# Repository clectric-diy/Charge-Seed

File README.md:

This breakout board is available for purchase at [store.clectric.diy](https://store.clectric.diy).

## Design
Our goal is to create a breakout board that includes the pinout diagram so that you have the reference information that you need to work with the Daisy Seed.

### 2D Render

### 3D Render

### Caveat
The PCB fabricator that we use requires the use of their proprietary software to add the images, so while the images are available here, there are extra steps to put them on the board.

## Feedback
Constructive [feedback](https://github.com/orgs/clectric-diy/discussions/categories/charge-seed-q-a) is welcome!

## License
This project is open hardware under the [CERN-OHL-S](https://gitlab.com/ohwr/project/cernohl/-/wikis/uploads/b236492596cfc91c12def7d50bbf7da0/cern_ohl_s_v2.pdf) license.

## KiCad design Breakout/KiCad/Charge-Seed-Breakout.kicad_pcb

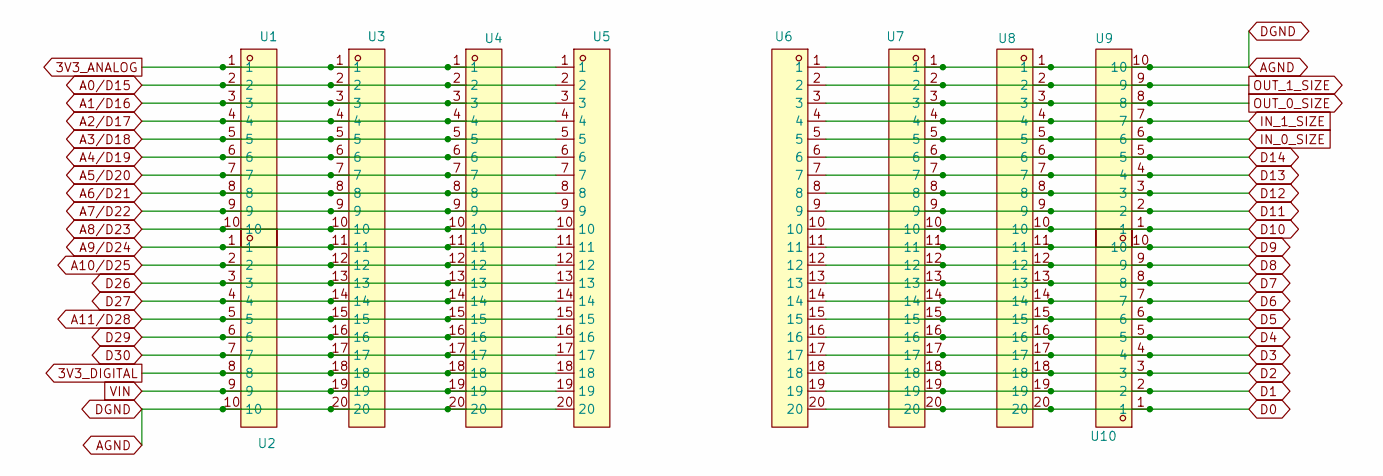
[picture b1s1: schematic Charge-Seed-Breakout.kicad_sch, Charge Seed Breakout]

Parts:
U1, U2, U9, U10: JL308-25410G01; CONN-TH_10P-P2.54_JILN_JL308-25410G01; LCSC Part C2922605
U3, U6: P125-1120A0BS116A1; HDR-TH_20P-P2.54-V-M-4; LCSC Part C19190492
U4, U5, U7, U8: 2541FV-20P-B; HDR-TH_20P-P2.54-V-F-2; LCSC Part C25503124

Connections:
3V3_ANALOG: U1.1, U3.1, U4.1, U5.1
3V3_DIGITAL: U2.8, U3.18, U4.18, U5.18
A0/D15: U1.2, U3.2, U4.2, U5.2
A1/D16: U1.3, U3.3, U4.3, U5.3
A2/D17: U1.4, U3.4, U4.4, U5.4
A3/D18: U1.5, U3.5, U4.5, U5.5
A4/D19: U1.6, U3.6, U4.6, U5.6
A5/D20: U1.7, U3.7, U4.7, U5.7
A6/D21: U1.8, U3.8, U4.8, U5.8
A7/D22: U1.9, U3.9, U4.9, U5.9
A8/D23: U1.10, U3.10, U4.10, U5.10
A9/D24: U2.1, U3.11, U4.11, U5.11
A10/D25: U2.2, U3.12, U4.12, U5.12
A11/D28: U2.5, U3.15, U4.15, U5.15
AGND: U2.10, U3.20, U4.20, U5.20, U6.1, U7.1, U8.1, U9.10
D0: U6.20, U7.20, U8.20, U10.1
D1: U6.19, U7.19, U8.19, U10.2
D2: U6.18, U7.18, U8.18, U10.3
D3: U6.17, U7.17, U8.17, U10.4
D4: U6.16, U7.16, U8.16, U10.5
D5: U6.15, U7.15, U8.15, U10.6
D6: U6.14, U7.14, U8.14, U10.7
D7: U6.13, U7.13, U8.13, U10.8
D8: U6.12, U7.12, U8.12, U10.9
D9: U6.11, U7.11, U8.11, U10.10
D10: U6.10, U7.10, U8.10, U9.1
D11: U6.9, U7.9, U8.9, U9.2
D12: U6.8, U7.8, U8.8, U9.3
D13: U6.7, U7.7, U8.7, U9.4
D14: U6.6, U7.6, U8.6, U9.5
D26: U2.3, U3.13, U4.13, U5.13
D27: U2.4, U3.14, U4.14, U5.14
D29: U2.6, U3.16, U4.16, U5.16
D30: U2.7, U3.17, U4.17, U5.17
IN_0_SIZE: U6.5, U7.5, U8.5, U9.6
IN_1_SIZE: U6.4, U7.4, U8.4, U9.7
OUT_0_SIZE: U6.3, U7.3, U8.3, U9.8
OUT_1_SIZE: U6.2, U7.2, U8.2, U9.9
VIN: U2.9, U3.19, U4.19, U5.19

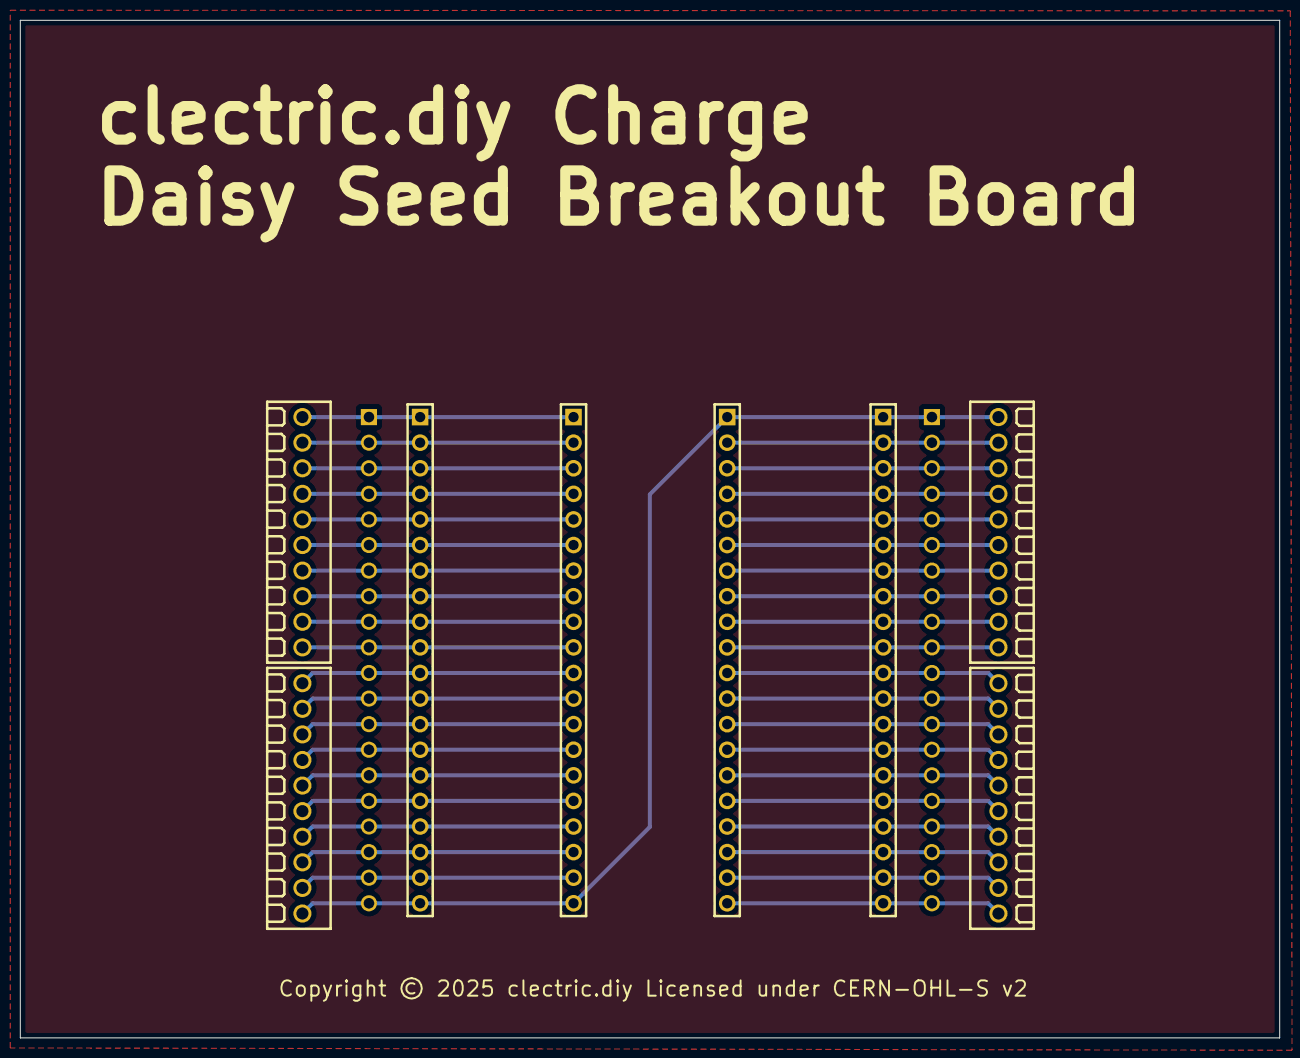
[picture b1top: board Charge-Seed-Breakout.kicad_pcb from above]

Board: 2 copper layers, 125.0 x 101.0 mm, 10 parts (0 on the bottom side), 39 nets.

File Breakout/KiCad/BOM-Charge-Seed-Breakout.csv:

"Id";"Designator";"Footprint";"Quantity";"Designation";"Supplier and ref";
1;"U8,U7,U4,U5";"HDR-TH_20P-P2.54-V-F-2";4;"2541FV-20P-B";;;
2;"U3,U6";"HDR-TH_20P-P2.54-V-M-4";2;"P125-1120A0BS116A1";;;
3;"U1,U9,U2,U10";"CONN-TH_10P-P2.54_JILN_JL308-25410G01";4;"JL308-25410G01";;;

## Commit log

2025-10-12 Starting fresh to get more reps with KiCad
2025-10-12 Seperated pinout diagram for JLCPCB Full Color silkscreen.
2025-10-12 Fresh start. Nearly complete.
2025-10-13 Exported as v0.1 for production.
2025-10-13 Reorganizing and renaming silkscreen files to clarify use.
2025-10-13 Shortening path.
2025-10-13 Updating site to share v0.1 prototype renders.
2025-10-13 Added caveat about silkscreening process.
2025-10-13 Clarified and cleaned up.
2025-10-13 Updated board's title in silkscreen to be correct.
2025-10-13 First commit of BOM
2025-10-24 Pinout updated on daisy.audio
2025-10-24 Missed pinout file
2025-10-24 Including footer note from daisy.audio and Copyright line
2025-10-27 Increased the trace width.
2025-10-27 Increased resolution of footer.
2026-01-16 ignoring production files. trust but verify.
2026-01-16 reducing to 2 layers
2026-02-09 Update README with purchase link and remove prototype
    Removed the prototype section and added purchase link.

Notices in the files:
Breakout/KiCad/Charge-Seed-Breakout.kicad_pcb:
Copyright © 2025 clectric.diy Licensed under CERN-OHL-S v2
